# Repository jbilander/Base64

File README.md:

# Base64
A 68k carrier board in DIP-64 that takes the [iCESugar-Pro-v1.3](https://github.com/wuxx/icesugar-pro) FPGA module

***

<br />

***

**Contents**

- [Hardware overview (Rev C)](#hardware-overview-rev-c)
- [Clock architecture](#clock-architecture)
- [Required module](#required-module)
- [Bill of materials](#bill-of-materials)
- [Build guide](#build-guide)
- [Status](#status)

***

## Hardware overview (Rev C)

- 4-layer PCB with continuous ground plane on layer 2 and +5V plane on layer 3
- iCESugar-Pro v1.3 FPGA module mounts via 200-pin SO-DIMM (DDR2) socket
- DIP-64 footprint, pin-compatible with the MC68000 socket in an Amiga 500 (or similar 68k host)
- 7× SN74CBTD3861 FET bus switches for bidirectional 5 V ↔ 3.3 V level translation on all bus signals
- Clock subsystem: 7 MHz host clock → 84 MHz phase-aligned output to the FPGA, locked to the host's 7 MHz with ~300 ps skew
- Autoconfig daisy-chain header (J2) — Amiga autoconfig is implemented and working; J2 must be jumpered or daisy-chained for the board to configure
- 3.3 V rail generated locally from the 5 V CPU socket supply via TLV75533 LDO

## Clock architecture

The host system provides a 7.09 MHz reference (E-clock derivative) on the CPU socket pin 15.
This is buffered by the 74LVC1G17 Schmitt-trigger gate (powered from the local 3.3 V rail,
with 5 V-tolerant inputs) and routed both to the FPGA at PT27A (C7, PCLKT0_1/+) and to the
ICS570B zero-delay clock multiplier (configured for 12× via floating S0/S1 with CLK/2
feedback).

The 570B produces a phase-aligned 84 MHz on CLK and 42 MHz on CLK/2. The 84 MHz output
feeds the FPGA at PL26A (L1, PCLKT6_1/HS+), which is well above the ECP5's 8 MHz PFD
minimum and locks reliably to the on-chip PLL. Inside the FPGA, the 84 MHz is divided
down to produce turbo CPU clocks (14 / 21 / 28 / 42 MHz) that remain phase-aligned to
the original 7 MHz reference.

## Required module

The Base64 carrier board requires an [iCESugar-Pro v1.3 FPGA module](https://github.com/wuxx/icesugar-pro) by Muse Lab, which mounts into the SO-DIMM socket (J1). The module carries the Lattice ECP5 LFE5U-25F-6BG256C FPGA along with onboard 32 MB SDRAM, 32 MB SPI flash, and an iCELink USB-C programmer.

Available from the official [Muse Lab AliExpress store](https://www.aliexpress.com/item/1005002270742248.html).

## Bill of materials

| Ref | Qty | Value / Part | Description | Package | Mouser P/N |
|-----|-----|--------------|-------------|---------|------------|
| U1 | 1 | ICS570BILF | Zero-delay clock multiplier with feedback (12× config) | SOIC-8 | [972-570BLFT](https://www.mouser.com/ProductDetail/972-570BLFT) |
| U2–U8 | 7 | SN74CBTD3861DGVR | 10-bit FET bus switch with 5 V→3.3 V diode level shift | TVSOP-24 | [595-SN74CBTD3861DGVR](https://www.mouser.com/ProductDetail/595-SN74CBTD3861DGVR) |
| U9 | 1 | SN74LVC1G17DBVR | Single Schmitt-trigger buffer, 5 V-tolerant inputs | SOT-23-5 | [595-SN74LVC1G17DBVR](https://www.mouser.com/ProductDetail/595-SN74LVC1G17DBVR) |
| U10 | 1 | TLV75533PDBVR | 3.3 V LDO regulator, 500 mA, fixed output | SOT-23-5 | [595-TLV75533PDBVR](https://www.mouser.com/ProductDetail/595-TLV75533PDBVR) |
| C1 | 1 | 1 µF | LDO input cap, X7R, 25 V | 0805 | [187-CL21B105KAFNNNE](https://www.mouser.com/ProductDetail/187-CL21B105KAFNNNE) |
| C2–C10 | 9 | 100 nF | CBTD / buffer / LDO output decoupling, X7R, 50 V | 0603 | [187-CL10B104KA8NNNC](https://www.mouser.com/ProductDetail/187-CL10B104KA8NNNC) |
| C11 | 1 | 10 nF | 570B VDD decoupling (per datasheet), X7R, 50 V | 0603 | [187-CL10B103KA8WPNC](https://www.mouser.com/ProductDetail/187-CL10B103KA8WPNC) |
| R1–R2 | 2 | 33 Ω | Series termination, 1% | 0805 | [652-CR0805FX-33R0ELF](https://www.mouser.com/ProductDetail/652-CR0805FX-33R0ELF) |
| R3–R4 | 2 | 33 Ω | Series termination, 1% | 0603 | [652-CR0603FX-33R0ELF](https://www.mouser.com/ProductDetail/652-CR0603FX-33R0ELF) |
| R5 | 1 | 10 kΩ | Autoconfig /CFGIN pull-up, 1% | 0603 | [652-CR0603FX-1002ELF](https://www.mouser.com/ProductDetail/652-CR0603FX-1002ELF) |
| J1 | 1 | TE 1473149-4 | 200-pin SO-DIMM (DDR2) socket for FPGA module | SMT | [571-1473149-4](https://www.mouser.com/ProductDetail/571-1473149-4) |
| J2 | 1 | 3-pin right-angle header | Autoconfig header (/CFGOUT, /CFGIN, GND), 0.64 mm square, 2.54 mm pitch | THT | [AliExpress](https://www.aliexpress.com/item/32963604292.html) |
| U11 | 2 | 40-pin breakaway male pin strip, 2.54 mm pitch | Round pins, ~11.96 mm overall pin length, used as DIP-64 CPU socket pins | THT | [AliExpress](https://www.aliexpress.com/item/32887861343.html) |

### Notes on selected parts

**U11 (CPU socket pins):** these are round male pins supplied as 40-pin breakaway pin strips on 2.54 mm pitch, with ~11.96 mm overall pin length (top of pin to bottom). Break each strip down to a 32-pin section — you need two such sections, so two strips minimum. See [step 8](#8-through-hole-parts) of the build guide for fitting them.

**J2 (autoconfig header):**
- Pin 1: /CFGOUT
- Pin 2: /CFGIN (with 10 kΩ pull-up via R5)
- Pin 3: GND

This header supports Amiga-style autoconfig daisy-chaining, and **autoconfig is implemented and working** in the current FPGA designs. J2 is therefore not optional — it has to be wired one of these two ways:

- **No other autoconfig device on the side expansion** (e.g. no A590): place a standard 2.54 mm jumper shunt across pin 2 (/CFGIN) and pin 3 (GND) so the Base64 autoconfigs immediately.
- **A side expansion autoconfig device is present**: connect that device's /CFGOUT to J2 pin 2 (/CFGIN) instead, so the devices daisy-chain in the expected order — side expansion configures first, then Base64.

If neither connection is made, R5 holds /CFGIN high, the board waits for its turn in the chain that never comes, and it will not appear to the system.

For use in non-Amiga 68k systems, J2 is not applicable in its standard form, though it could potentially be repurposed depending on the target system.

J2 uses a standard 0.64 mm square 2.54 mm pitch right-angle pin header. Available from AliExpress directly as a 3-pin part, or cut from a 40-pin breakaway strip.

***

## Build guide

This is how I build the board: everything hand-placed and hand-soldered, then a single pass
through a desktop reflow oven to even out the joints, and finally the through-hole parts.
It is not the only way to do it — see [alternative approaches](#alternative-approaches) if you
are building more than one or two boards — but it needs no stencil and no paste, and it
gives a clean, repeatable result.

Everything below assumes **leaded solder**. If you use lead-free you will need a
correspondingly hotter reflow profile.

### Tools and consumables

| | |
|---|---|
| Soldering iron | Temperature-controlled, with a 1 mm tip for the SO-DIMM pins |
| Solder (SMD + pins) | Stannol 518644 Sn60Pb40, 0.5 mm |
| Solder (GND pads) | Sn60Pb40, 1 mm |
| High-power iron | ZD-915 desoldering station, or any iron with enough thermal mass for a large ground pour |
| Reflow oven | T-962 desktop IR oven, or equivalent (hot plate / hot air with a proper profile) |
| Flux | No-clean flux, paste or pen |
| Kapton tape | For masking parts during high-heat steps |
| Cleaning | IPA, cotton buds, plus an electronics cleaner for the ICs (see [step 7](#7-inspect-and-clean)) |
| Inspection | Microscope or a decent magnifier |

### 1. Bus switches and their decoupling caps

Work in the order **C2, U2, C3, U3, C4, U4 … C8, U8** — one capacitor, then the IC it
decouples, then the next pair.

It is tempting to place all the capacitors in a single pass, but C2–C8 sit right next to the
drag-solder path along U2–U8. With all of them already fitted, drag-soldering the TVSOP-24
packages becomes much more awkward. Alternating keeps the area around each IC clear when you
need it.

### 2. Remaining passives and the small ICs

With the bus switches down, solder the resistors (R1–R5) and the remaining capacitors
(C1, C9, C10, C11). Then fit the three remaining ICs: **U9** (Schmitt buffer), **U10** (LDO)
and **U1** (clock multiplier).

### 3. SO-DIMM socket (J1)

Once all other surface-mount parts are on, place the SO-DIMM socket. There is a little
wiggle room in the footprint, so take the time to align and centre it as well as you can
against the silkscreen before tacking it down. Tack one corner, re-check the alignment along
the whole length, then tack the opposite corner.

### 4. The 200 signal pins

I solder these **pin by pin** rather than drag-soldering. The socket contacts are fine and
springy, and a drag tip tends to bend and flex them, which makes bridges easy and a clean
result hard.

Instead: use a 1 mm tip, flux the pins, pick up a small blob of solder on the tip and
transfer it to a pin — or two pins at a time once you find a rhythm. It is tedious, there is
no way around that. What matters is that every pin ends up with a small but definite amount
of solder on it.

Don't worry if the row looks uneven at this stage. The reflow step later will sort it out.

*Hand-soldering the 200 pins with 0.5 mm Sn60Pb40. Uneven at this point — that is expected.*

### 5. Retention arms to the large GND pads

The socket's two metal retention arms land on large ground pours, which sink far more heat
than a normal iron can deliver. I use the **ZD-915 desoldering station** for this because it
has the thermal capacity; a large chisel tip on a high-power iron will also work.

1. Cover **U8 and R5 with kapton tape** first — they sit close to the pad and you do not want to disturb them.
2. Flux both pads.
3. Feed roughly a centimetre of 1 mm Sn60Pb40 into the ZD-915 nozzle and set the station to **360 °C**.
4. Come in at an angle so the nozzle touches both the exposed part of the pad and the arm at the same time.
5. Hold with gentle pressure for **3–4 seconds** until the solder flows down and spreads across the pad, then lift off.

Be careful not to let the nozzle rest against the connector body — the plastic will melt.
As with the pins, the joint does not need to look pretty yet.

*ZD-915 at 360 °C on the ground pad, with U8 and R5 masked off under kapton tape.*

### 6. Reflow

At this point everything except the through-hole parts is soldered. Clean the spent flux off
the board, apply a fresh coat, and run it through the oven.

I use a **T-962 desktop IR oven** with the **Amtech SynTECH-LF** profile, which ramps to a
**240 °C peak** and then cools down.

*Two boards loaded in the T-962.*

*The Amtech SynTECH-LF profile as shown on the T-962.*

Gravity and surface tension do the rest — joints that looked lumpy going in come out even.

### 7. Inspect and clean

Inspect every pin under magnification: each should have a clean fillet, and there should be
no bridges anywhere along the socket.

Then clean the board with cotton buds and IPA.

**For the ICs, don't use neat IPA** — it lifts the laser marking off the packages. I use a
general-purpose electronics cleaner instead, with the compound:

> Hydrocarbons, C6-C7, n-alkanes, isoalkanes, cyclics, <5 % n-hexane, 2-Propanol

Applied to a clean cotton bud and wiped gently over the package, this cleans the ICs without
erasing the text the way 100 % IPA does.

*Electronics cleaner used on the ICs — cleans without taking the markings with it.*

*Two boards after reflow and cleanup.*

### 8. Through-hole parts

Last come the two 32-pin strips (**U11**) and the 3-pin CFG header (**J2**). Fit J2 — it is
required for the board to autoconfig, and you will need a jumper shunt for it unless you are
daisy-chaining from another device. See [notes on selected parts](#notes-on-selected-parts).

Push each 32-pin section through the carrier board pads **from the underside** and solder on the
top side. The protruding bottom side is what plugs into the host system's MC68000 socket.

The 32-pin sections are broken out of cheap 40-pin breakaway strips, and the break leaves a
rougher edge on that end. It makes no difference electrically, but it is a nice touch to
orient both strips so the **clean edges face the same way** — which of course puts both rough
edges on the other side.

*Clean edges on the same side …*

*… and the two broken edges together on the other.*

Finish with a final clean of the through-hole joints using cotton buds and IPA to remove the
excess flux.

### Alternative approaches

Hand-soldering the 200 pins is the slow way. Two alternatives worth considering:

- **Solder paste and hot air** on the SO-DIMM socket, with the connector's plastic body masked off with kapton tape so the hot air doesn't deform it.
- **Order a solder paste stencil** together with the PCBs. Then it becomes paste, place, reflow — and almost all of the hand work above disappears. Only worth it if you intend to build a batch.

### A note on the FPGA module

On my own iCESugar-Pro module I found a mark on the **25 MHz crystal oscillator** that looks
like it may have been made by a pin during installation of the module. I can't say for
certain where the dent came from, or whether it is a problem at all — it is worth a look
under a microscope if you have one. As a precaution I put a piece of kapton tape over the
oscillator.

*Kapton tape over the 25 MHz oscillator on the iCESugar-Pro module.*

***

## Status

Amiga autoconfig is implemented and working in the current FPGA designs — see the
[J2 notes](#notes-on-selected-parts) for the jumpering it requires.

Rev C changes vs Rev B:
- ICS501MLFT clock multiplier replaced with ICS570BLFT (adds feedback pin for phase-aligned operation)
- 74AHCT1G17 (5 V) replaced with 74LVC1G17 (3.3 V, 5 V-tolerant inputs)
- Added TLV75533 LDO to generate local 3.3 V rail
- Clock subsystem reworked for cleaner signal integrity (source-side series termination on every branch)
- 84 MHz output routed to FPGA's PL26A (L1, PCLKT6_1/HS+) clock-capable input

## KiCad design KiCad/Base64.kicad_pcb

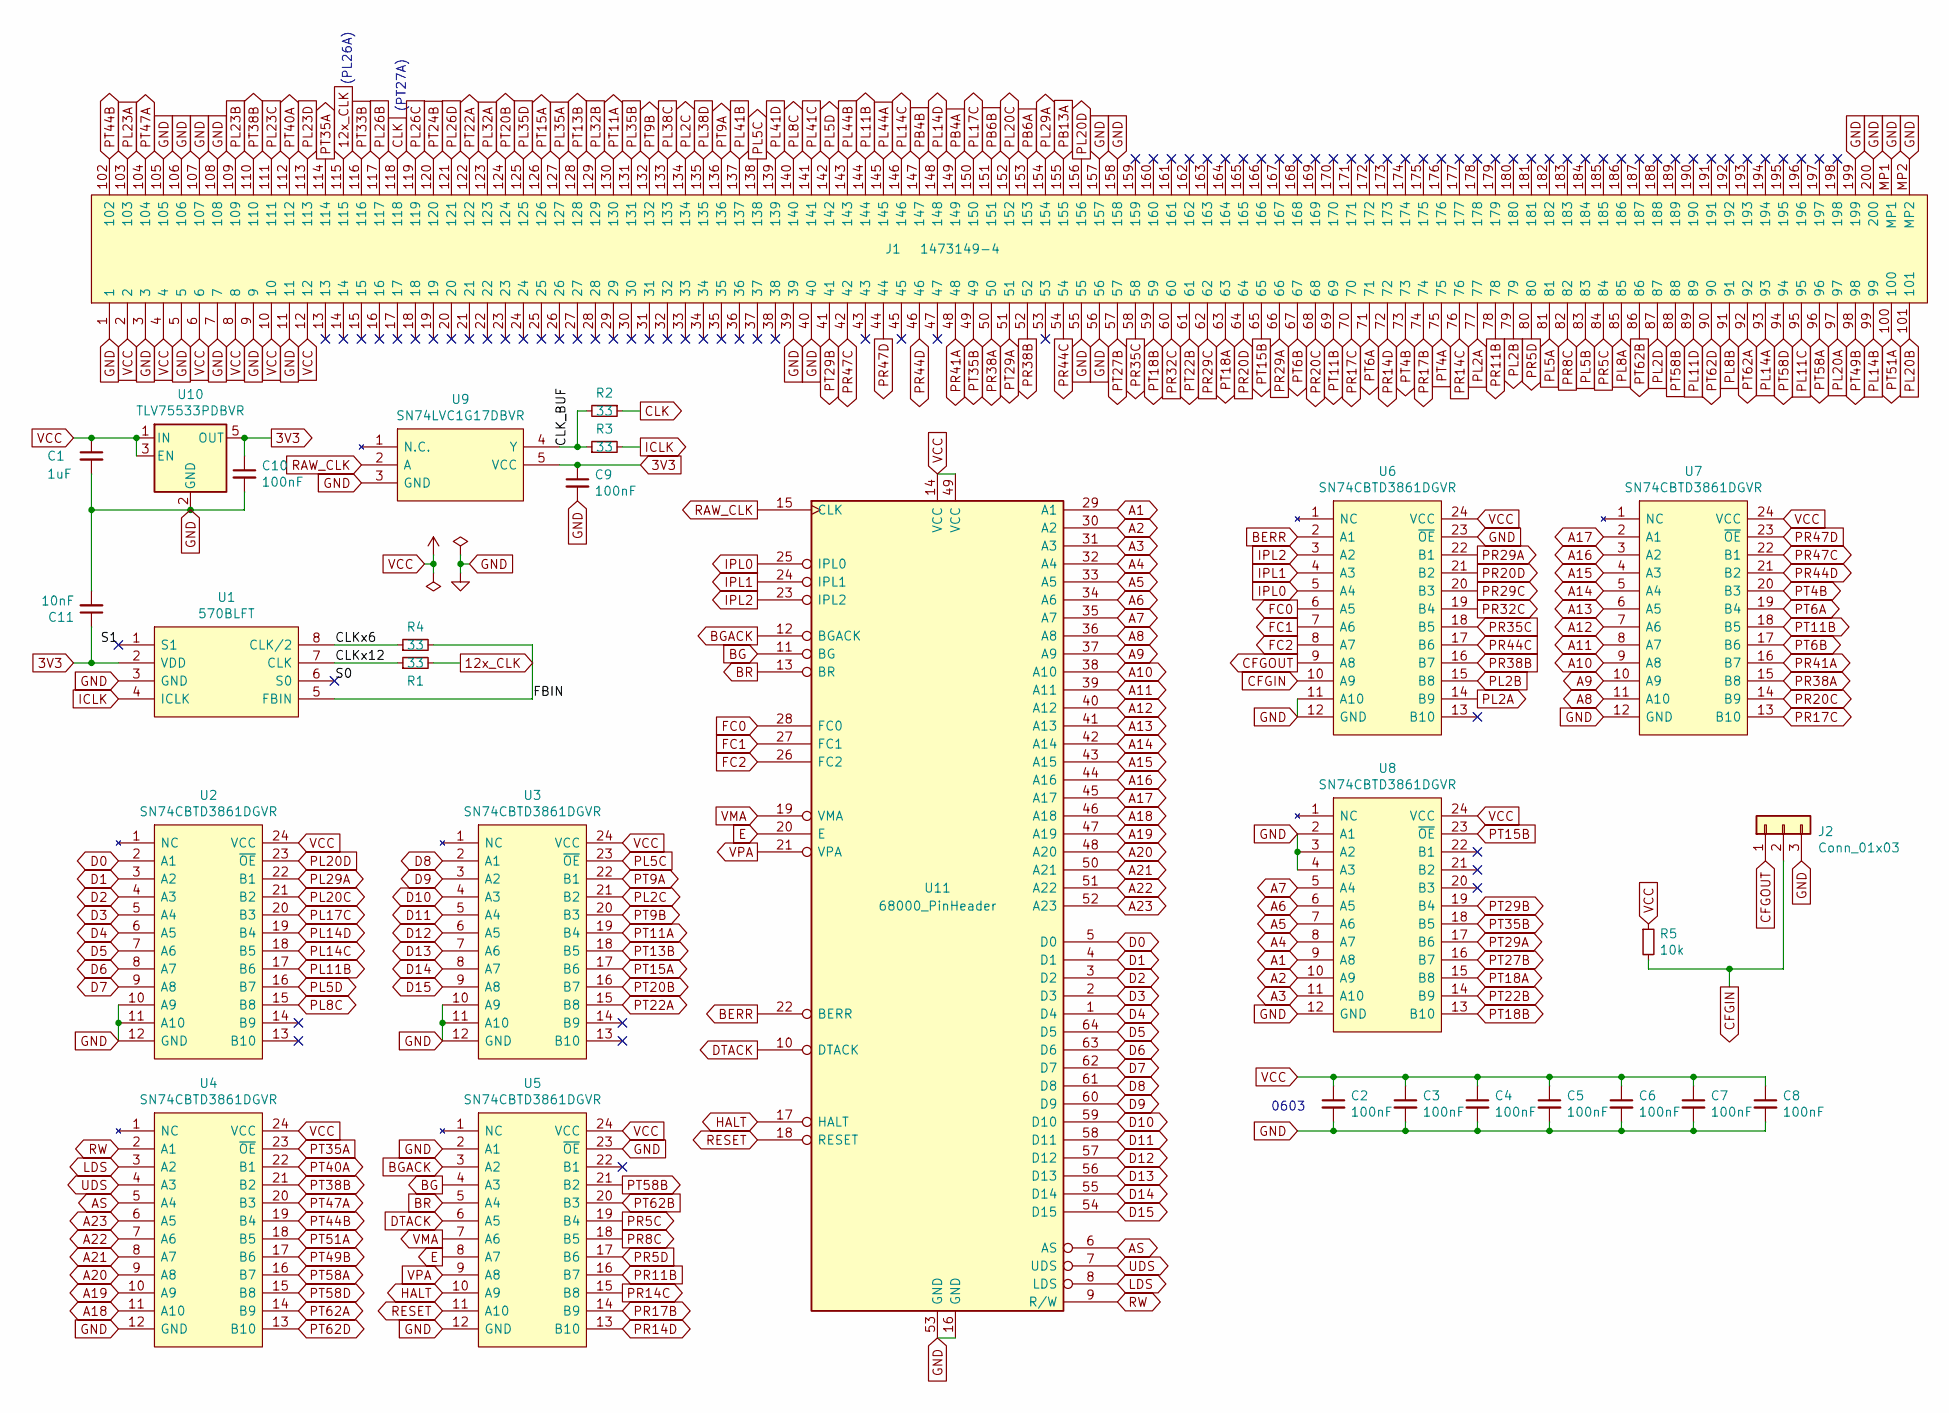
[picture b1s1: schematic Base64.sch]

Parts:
C1: 1uF; C_0805_2012Metric
C2, C3, C4, C5, C6, C7, C8, C9, C10: 100nF; C_0603_1608Metric
C11: 10nF; C_0603_1608Metric
J1: 1473149-4; TE_DDR2-SODIMM-200_1473149-x
J2: Conn_01x03; PinHeader_1x03_P2.54mm_Horizontal
R1, R2: 33; R_0805_2012Metric
R3, R4: 33; R_0603_1608Metric
R5: 10k; R_0603_1608Metric
U1: 570BLFT; SOIC-8_3.9x4.9mm_P1.27mm
U2, U3, U4, U5, U6, U7, U8: SN74CBTD3861DGVR; TSSOP-24_4.4x5mm_P0.4mm
U9: SN74LVC1G17DBVR; SOT95P280X145-5N
U10: TLV75533PDBVR; SOT-23-5
U11: 68000_PinHeader; DIP-64_W22.86mm

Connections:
3V3: C9.1, C10.1, C11.1, U1.2 (VDD), U9.5 (VCC), U10.5 (OUT)
12x_CLK: J1.115, R1.2
/CLK_BUF: R2.2, R3.1, U9.4 (Y)
/CLKx6: R4.1, U1.8 (CLK/2)
/CLKx12: R1.1, U1.7 (CLK)
/FBIN: R4.2, U1.5 (FBIN)
/S0: U1.6 (S0)
/S1: U1.1 (S1)
A1: U8.9 (A8), U11.29 (A1)
A2: U8.10 (A9), U11.30 (A2)
A3: U8.11 (A10), U11.31 (A3)
A4: U8.8 (A7), U11.32 (A4)
A5: U8.7 (A6), U11.33 (A5)
A6: U8.6 (A5), U11.34 (A6)
A7: U8.5 (A4), U11.35 (A7)
A8: U7.11 (A10), U11.36 (A8)
A9: U7.10 (A9), U11.37 (A9)
A10: U7.9 (A8), U11.38 (A10)
A11: U7.8 (A7), U11.39 (A11)
A12: U7.7 (A6), U11.40 (A12)
A13: U7.6 (A5), U11.41 (A13)
A14: U7.5 (A4), U11.42 (A14)
A15: U7.4 (A3), U11.43 (A15)
A16: U7.3 (A2), U11.44 (A16)
A17: U7.2 (A1), U11.45 (A17)
A18: U4.11 (A10), U11.46 (A18)
A19: U4.10 (A9), U11.47 (A19)
A20: U4.9 (A8), U11.48 (A20)
A21: U4.8 (A7), U11.50 (A21)
A22: U4.7 (A6), U11.51 (A22)
A23: U4.6 (A5), U11.52 (A23)
AS: U4.5 (A4), U11.6 (AS)
BERR: U6.2 (A1), U11.22 (BERR)
BG: U5.4 (A3), U11.11 (BG)
BGACK: U5.3 (A2), U11.12 (BGACK)
BR: U5.5 (A4), U11.13 (BR)
CFGIN: J2.2, R5.2, U6.10 (A9)
CFGOUT: J2.1, U6.9 (A8)
CLK: J1.118, R2.1
D0: U2.2 (A1), U11.5 (D0)
D1: U2.3 (A2), U11.4 (D1)
D2: U2.4 (A3), U11.3 (D2)
D3: U2.5 (A4), U11.2 (D3)
D4: U2.6 (A5), U11.1 (D4)
D5: U2.7 (A6), U11.64 (D5)
D6: U2.8 (A7), U11.63 (D6)
D7: U2.9 (A8), U11.62 (D7)
D8: U3.2 (A1), U11.61 (D8)
D9: U3.3 (A2), U11.60 (D9)
D10: U3.4 (A3), U11.59 (D10)
D11: U3.5 (A4), U11.58 (D11)
D12: U3.6 (A5), U11.57 (D12)
D13: U3.7 (A6), U11.56 (D13)
D14: U3.8 (A7), U11.55 (D14)
D15: U3.9 (A8), U11.54 (D15)
DTACK: U5.6 (A5), U11.10 (DTACK)
E: U5.8 (A7), U11.20 (E)
FC0: U6.6 (A5), U11.28 (FC0)
FC1: U6.7 (A6), U11.27 (FC1)
FC2: U6.8 (A7), U11.26 (FC2)
GND: C1.2, C2.2, C3.2, C4.2, C5.2, C6.2, C7.2, C8.2, C9.2, C10.2, C11.2, J1.1, J1.3, J1.5, J1.7, J1.9, J1.11, J1.39, J1.40, J1.55, J1.56, J1.105, J1.106, J1.107, J1.108, J1.157, J1.158, J1.199, J1.200, J1.MP1, J1.MP2, J2.3, U1.3 (GND), U2.10 (A9), U2.11 (A10), U2.12 (GND), U3.10 (A9), U3.11 (A10), U3.12 (GND), U4.12 (GND), U5.2 (A1), U5.12 (GND), U5.23 (~OE), U6.11 (A10), U6.12 (GND), U6.23 (~OE), U7.12 (GND), U8.2 (A1), U8.3 (A2), U8.4 (A3), U8.12 (GND), U9.3 (GND), U10.2 (GND), U11.16 (GND), U11.53 (GND)
HALT: U5.10 (A9), U11.17 (HALT)
ICLK: R3.2, U1.4 (ICLK)
IPL0: U6.5 (A4), U11.25 (IPL0)
IPL1: U6.4 (A3), U11.24 (IPL1)
IPL2: U6.3 (A2), U11.23 (IPL2)
LDS: U4.3 (A2), U11.8 (LDS)
PB4A: J1.149
PB4B: J1.147
PB6A: J1.153
PB6B: J1.151
PB13A: J1.155
PL2A: J1.77, U6.14 (B9)
PL2B: J1.79, U6.15 (B8)
PL2C: J1.134, U3.21 (B2)
PL2D: J1.87
PL5A: J1.81
PL5B: J1.83
PL5C: J1.138, U3.23 (~OE)
PL5D: J1.142, U2.16 (B7)
PL8A: J1.85
PL8B: J1.91
PL8C: J1.140, U2.15 (B8)
PL11B: J1.144, U2.17 (B6)
PL11C: J1.95
PL11D: J1.89
PL14A: J1.93
PL14B: J1.99
PL14C: J1.146, U2.18 (B5)
PL14D: J1.148, U2.19 (B4)
PL17C: J1.150, U2.20 (B3)
PL20A: J1.97
PL20B: J1.101
PL20C: J1.152, U2.21 (B2)
PL20D: J1.156, U2.23 (~OE)
PL23A: J1.103
PL23B: J1.109
PL23C: J1.111
PL23D: J1.113
PL26B: J1.117
PL26C: J1.119
PL26D: J1.121
PL29A: J1.154, U2.22 (B1)
PL32A: J1.123
PL32B: J1.129
PL35A: J1.127
PL35B: J1.131
PL35D: J1.125
PL38C: J1.133
PL38D: J1.135
PL41B: J1.137
PL41C: J1.141
PL41D: J1.139
PL44A: J1.145
PL44B: J1.143
PR5C: J1.84, U5.19 (B4)
PR5D: J1.80, U5.17 (B6)
PR8C: J1.82, U5.18 (B5)
PR11B: J1.78, U5.16 (B7)
PR14C: J1.76, U5.15 (B8)
PR14D: J1.72, U5.13 (B10)
PR17B: J1.74, U5.14 (B9)
PR17C: J1.70, U7.13 (B10)
PR20C: J1.68, U7.14 (B9)
PR20D: J1.64, U6.21 (B2)
PR29A: J1.66, U6.22 (B1)
PR29C: J1.62, U6.20 (B3)
PR32C: J1.60, U6.19 (B4)
PR35C: J1.58, U6.18 (B5)
PR38A: J1.50, U7.15 (B8)
PR38B: J1.52, U6.16 (B7)
PR41A: J1.48, U7.16 (B7)
PR44C: J1.54, U6.17 (B6)
PR44D: J1.46, U7.21 (B2)
PR47C: J1.42, U7.22 (B1)
PR47D: J1.44, U7.23 (~OE)
PT4A: J1.75
PT4B: J1.73, U7.20 (B3)
PT6A: J1.71, U7.19 (B4)
PT6B: J1.67, U7.17 (B6)
PT9A: J1.136, U3.22 (B1)
PT9B: J1.132, U3.20 (B3)
PT11A: J1.130, U3.19 (B4)
PT11B: J1.69, U7.18 (B5)
PT13B: J1.128, U3.18 (B5)
PT15A: J1.126, U3.17 (B6)
PT15B: J1.65, U8.23 (~OE)
PT18A: J1.63, U8.15 (B8)
PT18B: J1.59, U8.13 (B10)
PT20B: J1.124, U3.16 (B7)
PT22A: J1.122, U3.15 (B8)
PT22B: J1.61, U8.14 (B9)
PT24B: J1.120
PT27B: J1.57, U8.16 (B7)
PT29A: J1.51, U8.17 (B6)
PT29B: J1.41, U8.19 (B4)
PT33B: J1.116
PT35A: J1.114, U4.23 (~OE)
PT35B: J1.49, U8.18 (B5)
PT38B: J1.110, U4.21 (B2)
PT40A: J1.112, U4.22 (B1)
PT44B: J1.102, U4.19 (B4)
PT47A: J1.104, U4.20 (B3)
PT49B: J1.98, U4.17 (B6)
PT51A: J1.100, U4.18 (B5)
PT58A: J1.96, U4.16 (B7)
PT58B: J1.88, U5.21 (B2)
PT58D: J1.94, U4.15 (B8)
PT62A: J1.92, U4.14 (B9)
PT62B: J1.86, U5.20 (B3)
PT62D: J1.90, U4.13 (B10)
RAW_CLK: U9.2 (A), U11.15 (CLK)
RESET: U5.11 (A10), U11.18 (RESET)
RW: U4.2 (A1), U11.9 (R/W)
UDS: U4.4 (A3), U11.7 (UDS)
VCC: C1.1, C2.1, C3.1, C4.1, C5.1, C6.1, C7.1, C8.1, J1.2, J1.4, J1.6, J1.8, J1.10, J1.12, R5.1, U2.24 (VCC), U3.24 (VCC), U4.24 (VCC), U5.24 (VCC), U6.24 (VCC), U7.24 (VCC), U8.24 (VCC), U10.1 (IN), U10.3 (EN), U11.14 (VCC), U11.49 (VCC)
VMA: U5.7 (A6), U11.19 (VMA)
VPA: U5.9 (A8), U11.21 (VPA)

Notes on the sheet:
(PL26A)
(PT27A)
0603

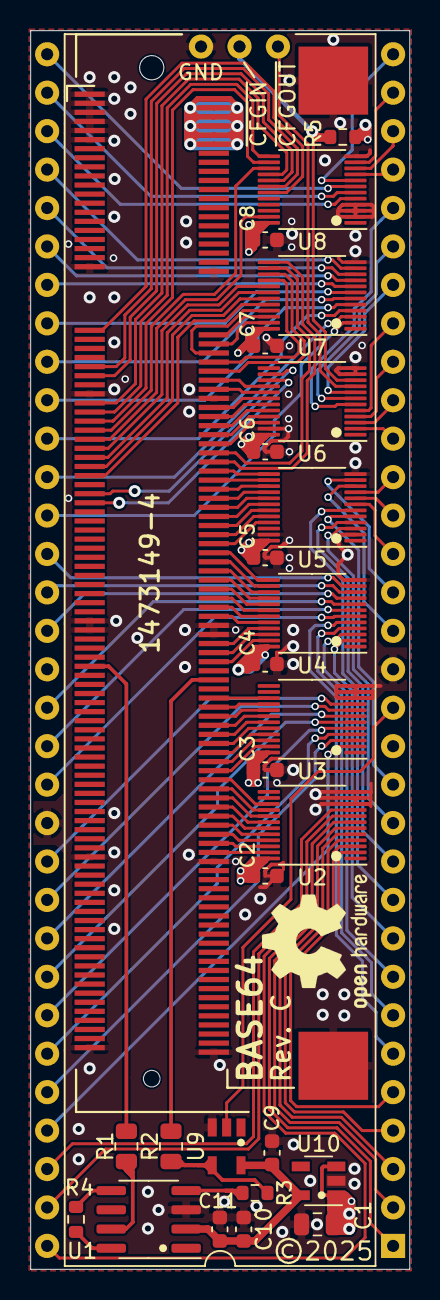
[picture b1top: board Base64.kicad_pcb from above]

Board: 4 copper layers, 25.1 x 81.8 mm, 29 parts (1 on the bottom side), 138 nets.

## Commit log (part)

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2025-09-28 Add to .gitignore
2025-09-28 Add KiCad files
2025-09-28 Add 3D-model of TE_DDR2-SODIMM-200_1473149
2025-10-28 Add 0.35 mm trace width
2025-10-28 Add 501MLFT, SN74CBTD3861DGVR, Generic_Conn_01x03, C_Small and R_Small
2025-10-28 Add 501MLFT and SN74CBTD3861DGVR
2025-10-28 Add footprint
2025-10-28 Add 3D model of pin strip
2025-10-28 more placement and routing
2025-10-28 silkscreen fixes, adding a dot to indicate pin 1 on all IC footprints
2025-10-28 Add value (10k) to R2 pull-up resistor and some small routing improvements
2025-10-28 Add PlotDirectory
2025-10-28 Add schematic
2025-10-28 Add KiCad screenshots
2025-10-28 Add license
2025-10-28 rename file
2025-10-29 Fixed typo on CFGOUT net and corrected signal direction on many nets
2025-10-29 Add schematic pdf
2025-10-30 Small silkscreen fix on underside
2025-10-31 Add 74AHCT1G17 symbol
2025-10-31 Add a 74AHCT1G17 buffering the raw 7 MHz clk and fanout to the 501 PLL (U1) and a pin in the CBTD (U6) that propagates to PL23A (J1 on the FPGA)
2025-10-31 Add revB schematic pdf
2025-11-02 Small silkscreen fixes and routing/VCC/GND-stitching improvements, better positioning of CFG-header
2025-11-02 Add a GND via
2025-11-02 Update with revB screenshots
2025-11-02 Add more screenshots
2025-11-19 Change J1 value from 1473149-1 (SO-DIMM DDR) to 1473149-4 (SO-DIMM DDR2) as keying is different and iCESugar-Pro module is of DDR2 type.
2025-11-19 Change J1 value from 1473149-1 (SO-DIMM DDR) to 1473149-4 (SO-DIMM DDR2)
2026-06-06 Add 3D model
2026-06-06 Add 570BLFT and SN74LVC1G17DBVR symbols to library
2026-06-06 Redesign with 570BLFT in order to generate a phase aligned 84 MHz clock
2026-06-07 Add text notes for CLK lines
2026-06-07 Improve via GND-stitching around U1 and remove JLCJLCJLCJLC silkscreen label
2026-06-08 Silkscreen fix, add dot for pin 1 on U10
2026-06-09 Add Rev C schematic pdf
2026-06-09 Update README.md
    Update with BOM for Rev C.
2026-06-09 Update screenshots with Rev. C

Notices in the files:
KiCad/Base64.kicad_pcb:
CC BY-SA 4.0
©2025
